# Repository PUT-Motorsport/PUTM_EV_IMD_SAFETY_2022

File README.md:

# PUTM_EV_IMD_SAFETY_2022
Board for handling Bender Insulation Measuring Device, enabling openig shutdown circuit in case of Trackive System potencial shortening to LV ground

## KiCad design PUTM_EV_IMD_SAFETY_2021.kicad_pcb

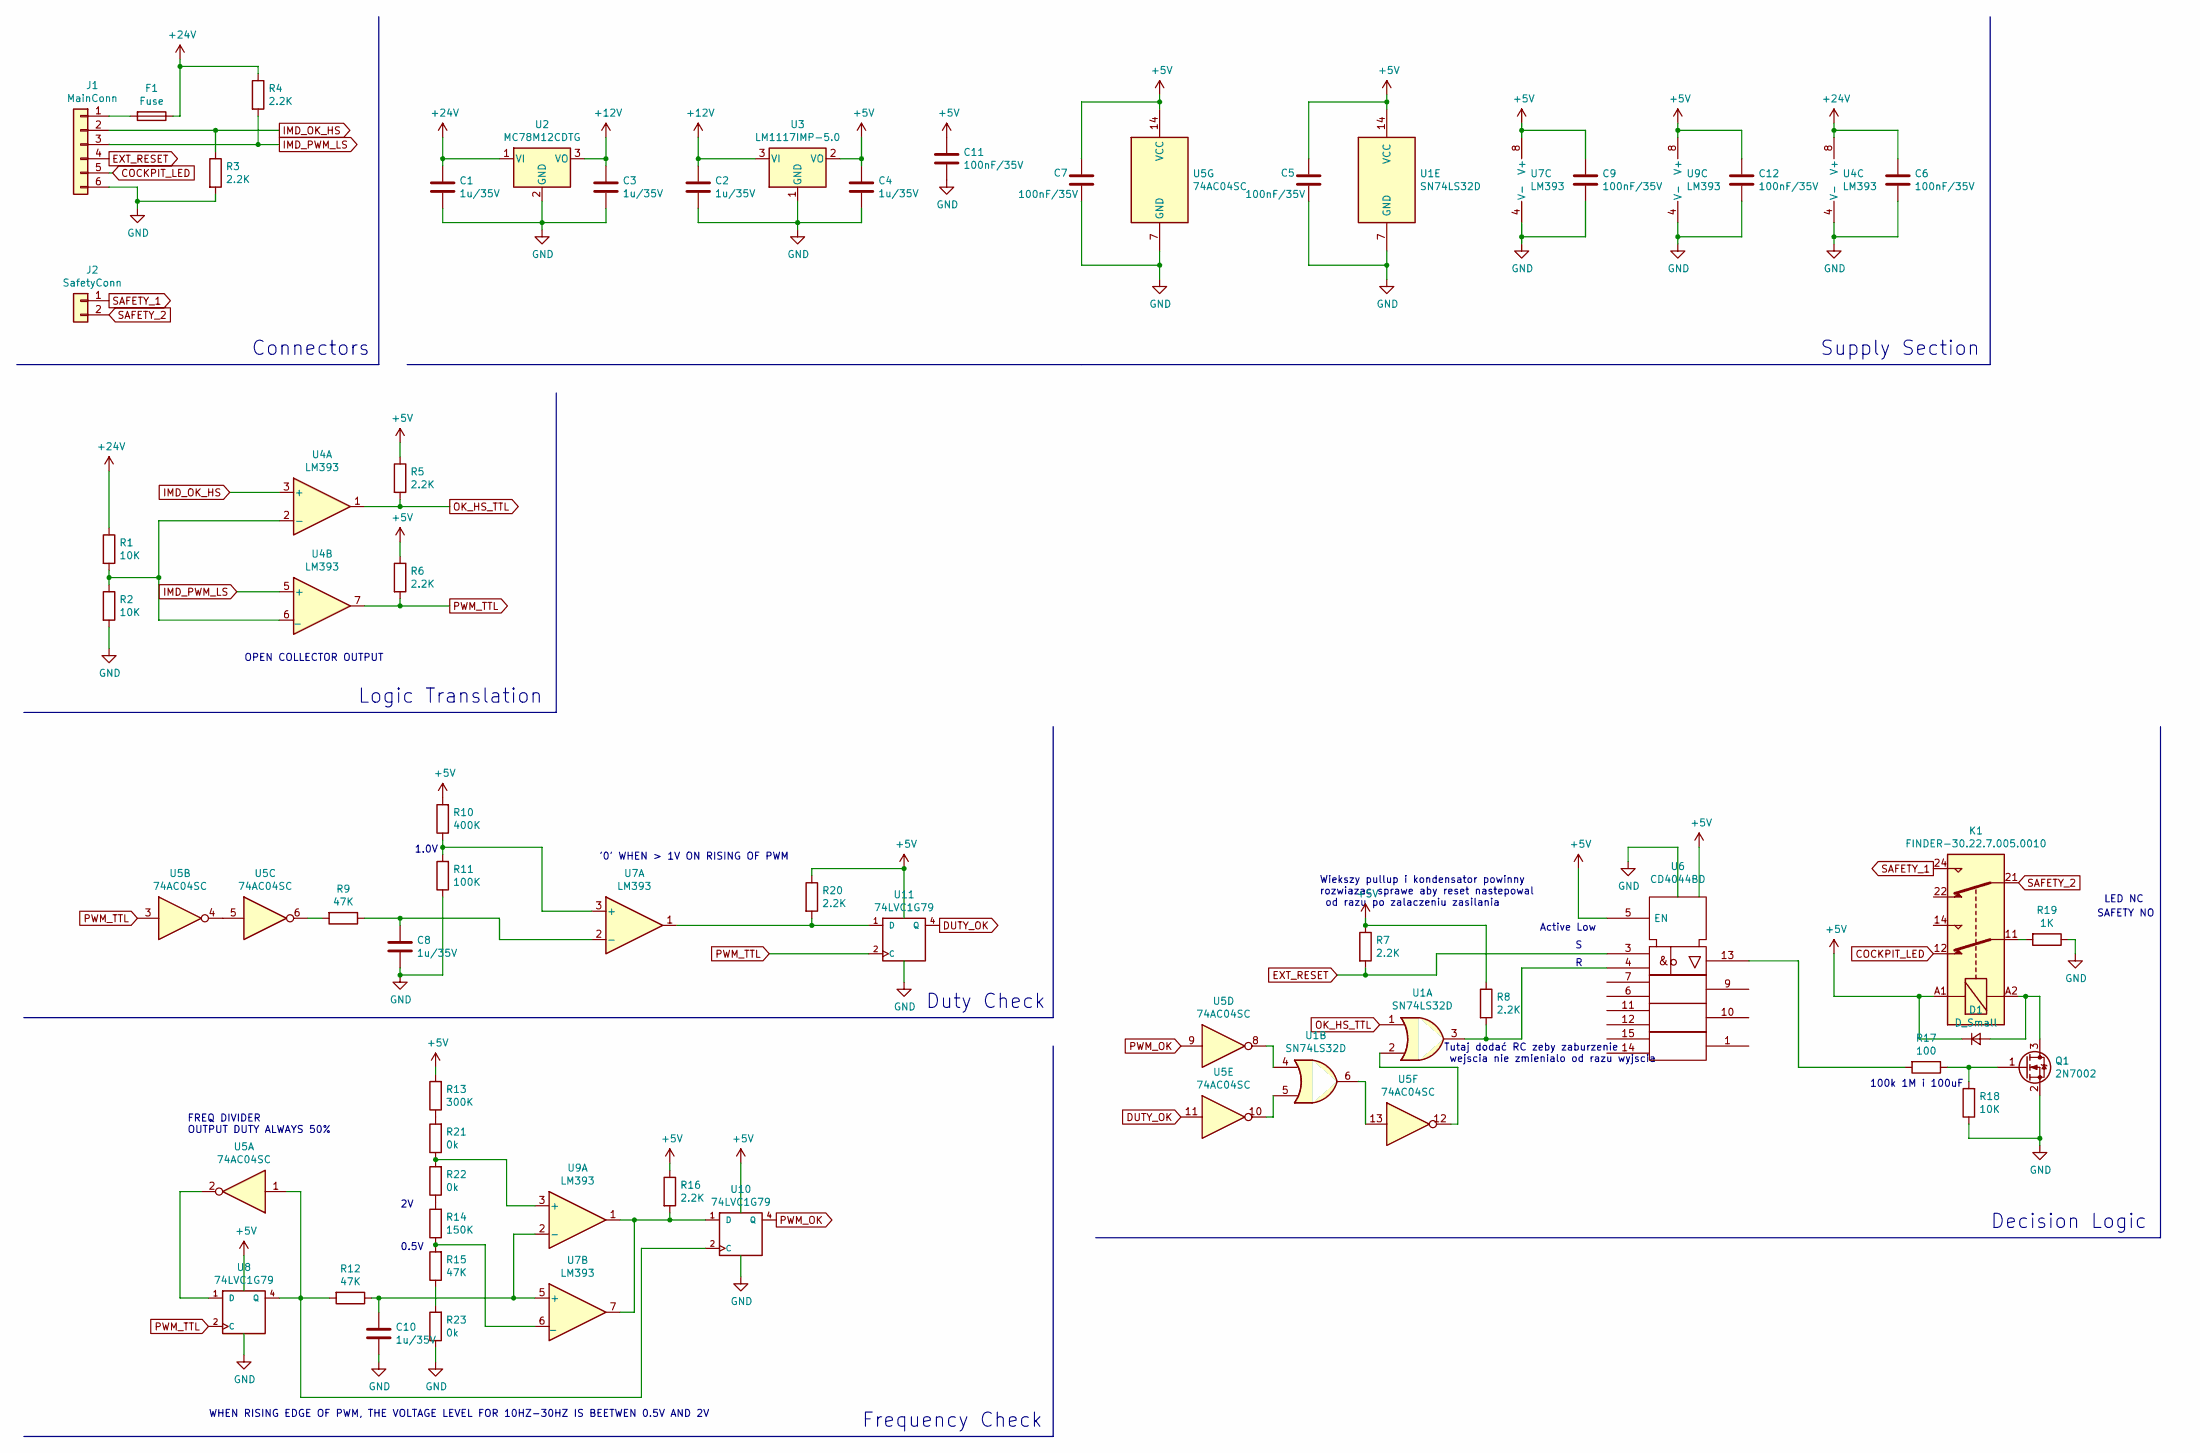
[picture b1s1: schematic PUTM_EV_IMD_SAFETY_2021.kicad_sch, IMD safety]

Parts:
C1, C2, C3, C4, C8, C10: 1u/35V; C_1206_3216Metric
C5, C6, C7, C9, C11, C12: 100nF/35V; C_1206_3216Metric
D1: D_Small; D_SMB
F1: Fuse; Fuse_1812_4532Metric
J1: MainConn; Molex_Micro-Fit_3.0_43650-0600_1x06_P3.00mm_Horizontal
J2: SafetyConn; Molex_Micro-Fit_3.0_43650-0200_1x02_P3.00mm_Horizontal
K1: FINDER-30.22.7.005.0010; Relay_DPDT_Finder_30.22
Q1: 2N7002; SOT-23
R1, R2, R18: 10K; R_1206_3216Metric
R3, R4, R5, R6, R7, R8, R16, R20: 2.2K; R_1206_3216Metric
R9, R12, R15: 47K; R_1206_3216Metric
R10: 400K; R_1206_3216Metric
R11: 100K; R_1206_3216Metric
R13: 300K; R_1206_3216Metric
R14: 150K; R_1206_3216Metric
R17: 100; R_1206_3216Metric
R19: 1K; R_1206_3216Metric
R21, R22, R23: 0k; R_1206_3216Metric
U1: SN74LS32D; SOIC-14_3.9x8.7mm_P1.27mm
U2: MC78M12CDTG; TO-252-3_TabPin2
U3: LM1117IMP-5.0; SOT-223-3_TabPin2
U4, U7, U9: LM393; SO-8_3.9x4.9mm_P1.27mm
U5: 74AC04SC; SOIC-14_3.9x8.7mm_P1.27mm
U6: CD4044BD; SOP-16_4.55x10.3mm_P1.27mm
U8, U10, U11: 74LVC1G79; SOT-23-5

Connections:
+5V: C4.1, C5.1, C7.1, C9.1, C11.1, C12.1, D1.1 (K), K1.A1, R5.1, R6.1, R7.1, R8.1, R10.2, R13.2, R16.1, R20.1, U1.14 (VCC), U3.2 (VO), U5.14 (VCC), U6.5 (EN), U6.16 (Vdd), U7.8 (V+), U8.5 (VCC), U9.8 (V+), U10.5 (VCC), U11.5 (VCC)
+12V: C2.1, C3.1, U2.3 (VO), U3.3 (VI)
+24V: C1.1, C6.1, F1.1, R1.1, R4.1, U2.1 (VI), U4.8 (V+)
COCKPIT_LED: J1.5, K1.12
DUTY_OK: U5.11, U11.4 (Q)
EXT_RESET: J1.4, R7.2, U6.3
GND: C1.2, C2.2, C3.2, C4.2, C5.2, C6.2, C7.2, C8.2, C9.2, C10.2, C11.2, C12.2, J1.6, Q1.2 (S), R2.2, R3.2, R11.1, R18.1, R19.1, R23.1, U1.7 (GND), U2.2 (GND), U3.1 (GND), U4.4 (V-), U5.7 (GND), U6.8 (Vss), U7.4 (V-), U8.3 (GND), U9.4 (V-), U10.3 (GND), U11.3 (GND)
IMD_OK_HS: J1.2, R3.1, U4.3 (+)
IMD_PWM_LS: J1.3, R4.2, U4.5 (+)
unnamed: C8.1, R9.1, U7.2 (-)
unnamed: C10.1, R12.1, U7.5 (+), U9.2 (-)
unnamed: D1.2 (A), K1.A2, Q1.3 (D)
unnamed: F1.2, J1.1
unnamed: K1.11, R19.2
unnamed: Q1.1 (G), R17.1, R18.2
unnamed: R1.2, R2.1, U4.2 (-), U4.6 (_)
unnamed: R8.2, U1.3, U6.4
unnamed: R9.2, U5.6
unnamed: R10.1, R11.2, U7.3 (+)
unnamed: R12.2, U5.1, U8.4 (Q), U10.2 (C)
unnamed: R13.1, R21.2
unnamed: R14.1, R15.2, U7.6 (_)
unnamed: R14.2, R22.1
unnamed: R15.1, R23.2
unnamed: R16.2, U7.7, U9.1, U10.1 (D)
unnamed: R17.2, U6.13
unnamed: R20.2, U7.1, U11.1 (D)
unnamed: R21.1, R22.2, U9.3 (+)
unnamed: U1.2, U5.12
unnamed: U1.4, U5.8
unnamed: U1.5, U5.10
unnamed: U1.6, U5.13
unnamed: U5.2, U8.1 (D)
unnamed: U5.4, U5.5
OK_HS_TTL: R5.2, U1.1, U4.1
PWM_OK: U5.9, U10.4 (Q)
PWM_TTL: R6.2, U4.7, U5.3, U8.2 (C), U11.2 (C)
SAFETY_1: J2.1, K1.24
SAFETY_2: J2.2, K1.21

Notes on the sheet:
Active Low
Wiekszy pullup i kondensator powinny rozwiazac sprawe aby reset nastepowal od razu po zalaczeniu zasilania
Decision Logic
Supply Section
Tutaj dodać RC zeby zaburzenie wejscia nie zmienialo od razu wyjscia
LED NC
Frequency Check
OPEN COLLECTOR OUTPUT
FREQ DIVIDER OUTPUT DUTY ALWAYS 50%
100k 1M i 100uF
0.5V
SAFETY NO
'0' WHEN > 1V ON RISING OF PWM
Connectors
Duty Check
Logic Translation
1.0V
WHEN RISING EDGE OF PWM, THE VOLTAGE LEVEL FOR 10HZ-30HZ IS BEETWEN 0.5V AND 2V

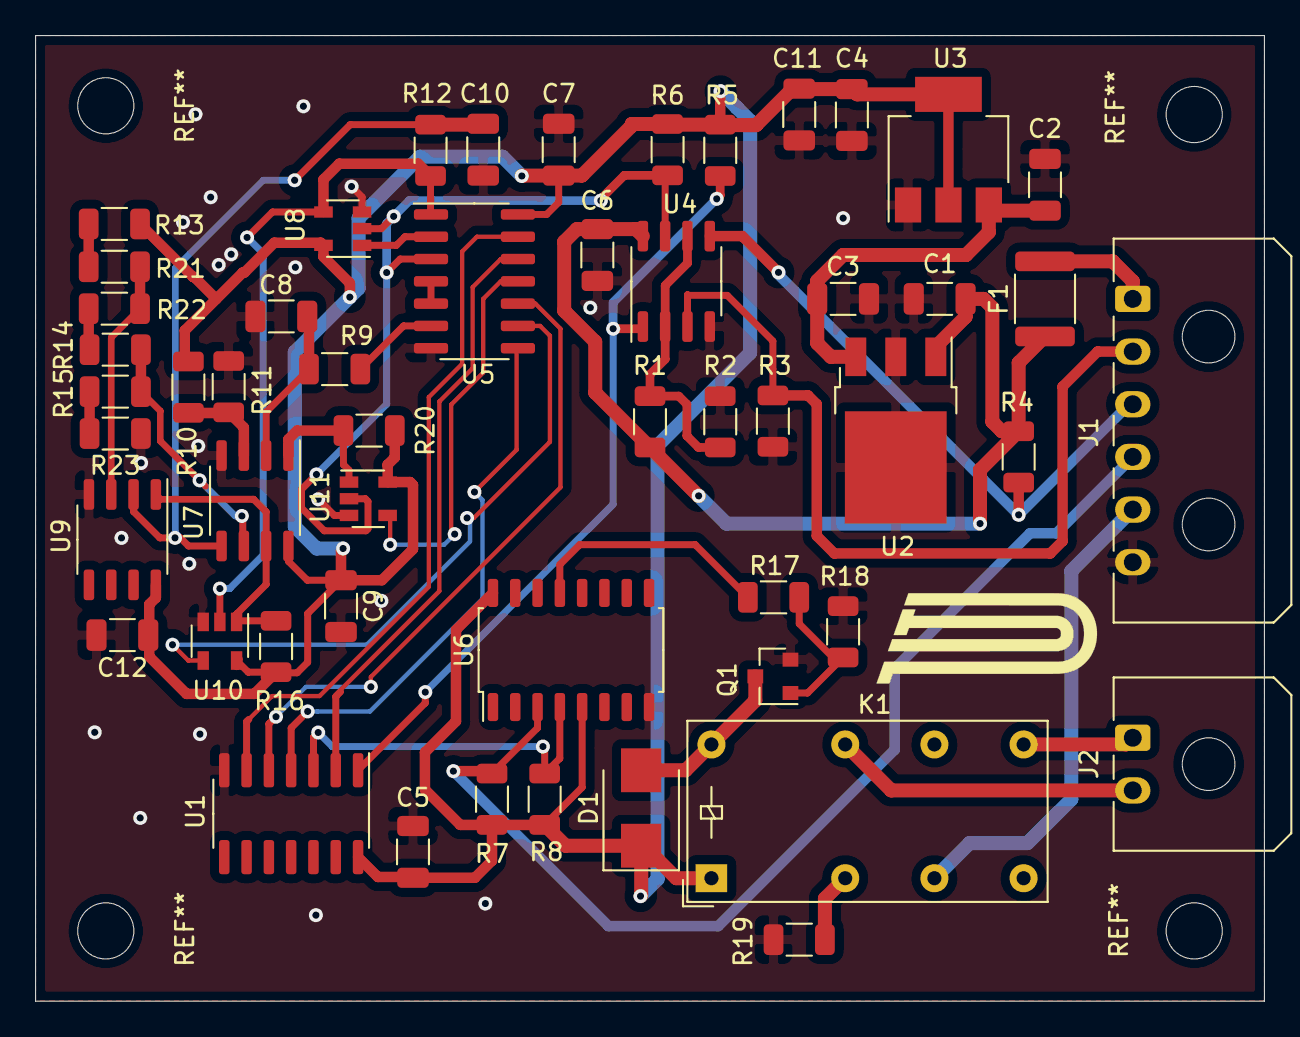
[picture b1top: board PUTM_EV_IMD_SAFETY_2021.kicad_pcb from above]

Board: 2 copper layers, 70.0 x 55.0 mm, 52 parts (0 on the bottom side), 39 nets.

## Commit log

2022-03-08 Transfer from Podio
2022-06-04 Added signatures libraries
2022-06-04 schematic edited - changed comparator ladder connections
2022-06-04 PCB Routed and signed with v2 version
2022-08-01 Project converted to Kicad6, Schematic beatuyfing
2022-08-01 Added autoreset into schematic
2022-08-01 Schematic upgraded with hard wired componets
2022-08-01 Schematic patch
2022-08-01 changes of schematic components values
